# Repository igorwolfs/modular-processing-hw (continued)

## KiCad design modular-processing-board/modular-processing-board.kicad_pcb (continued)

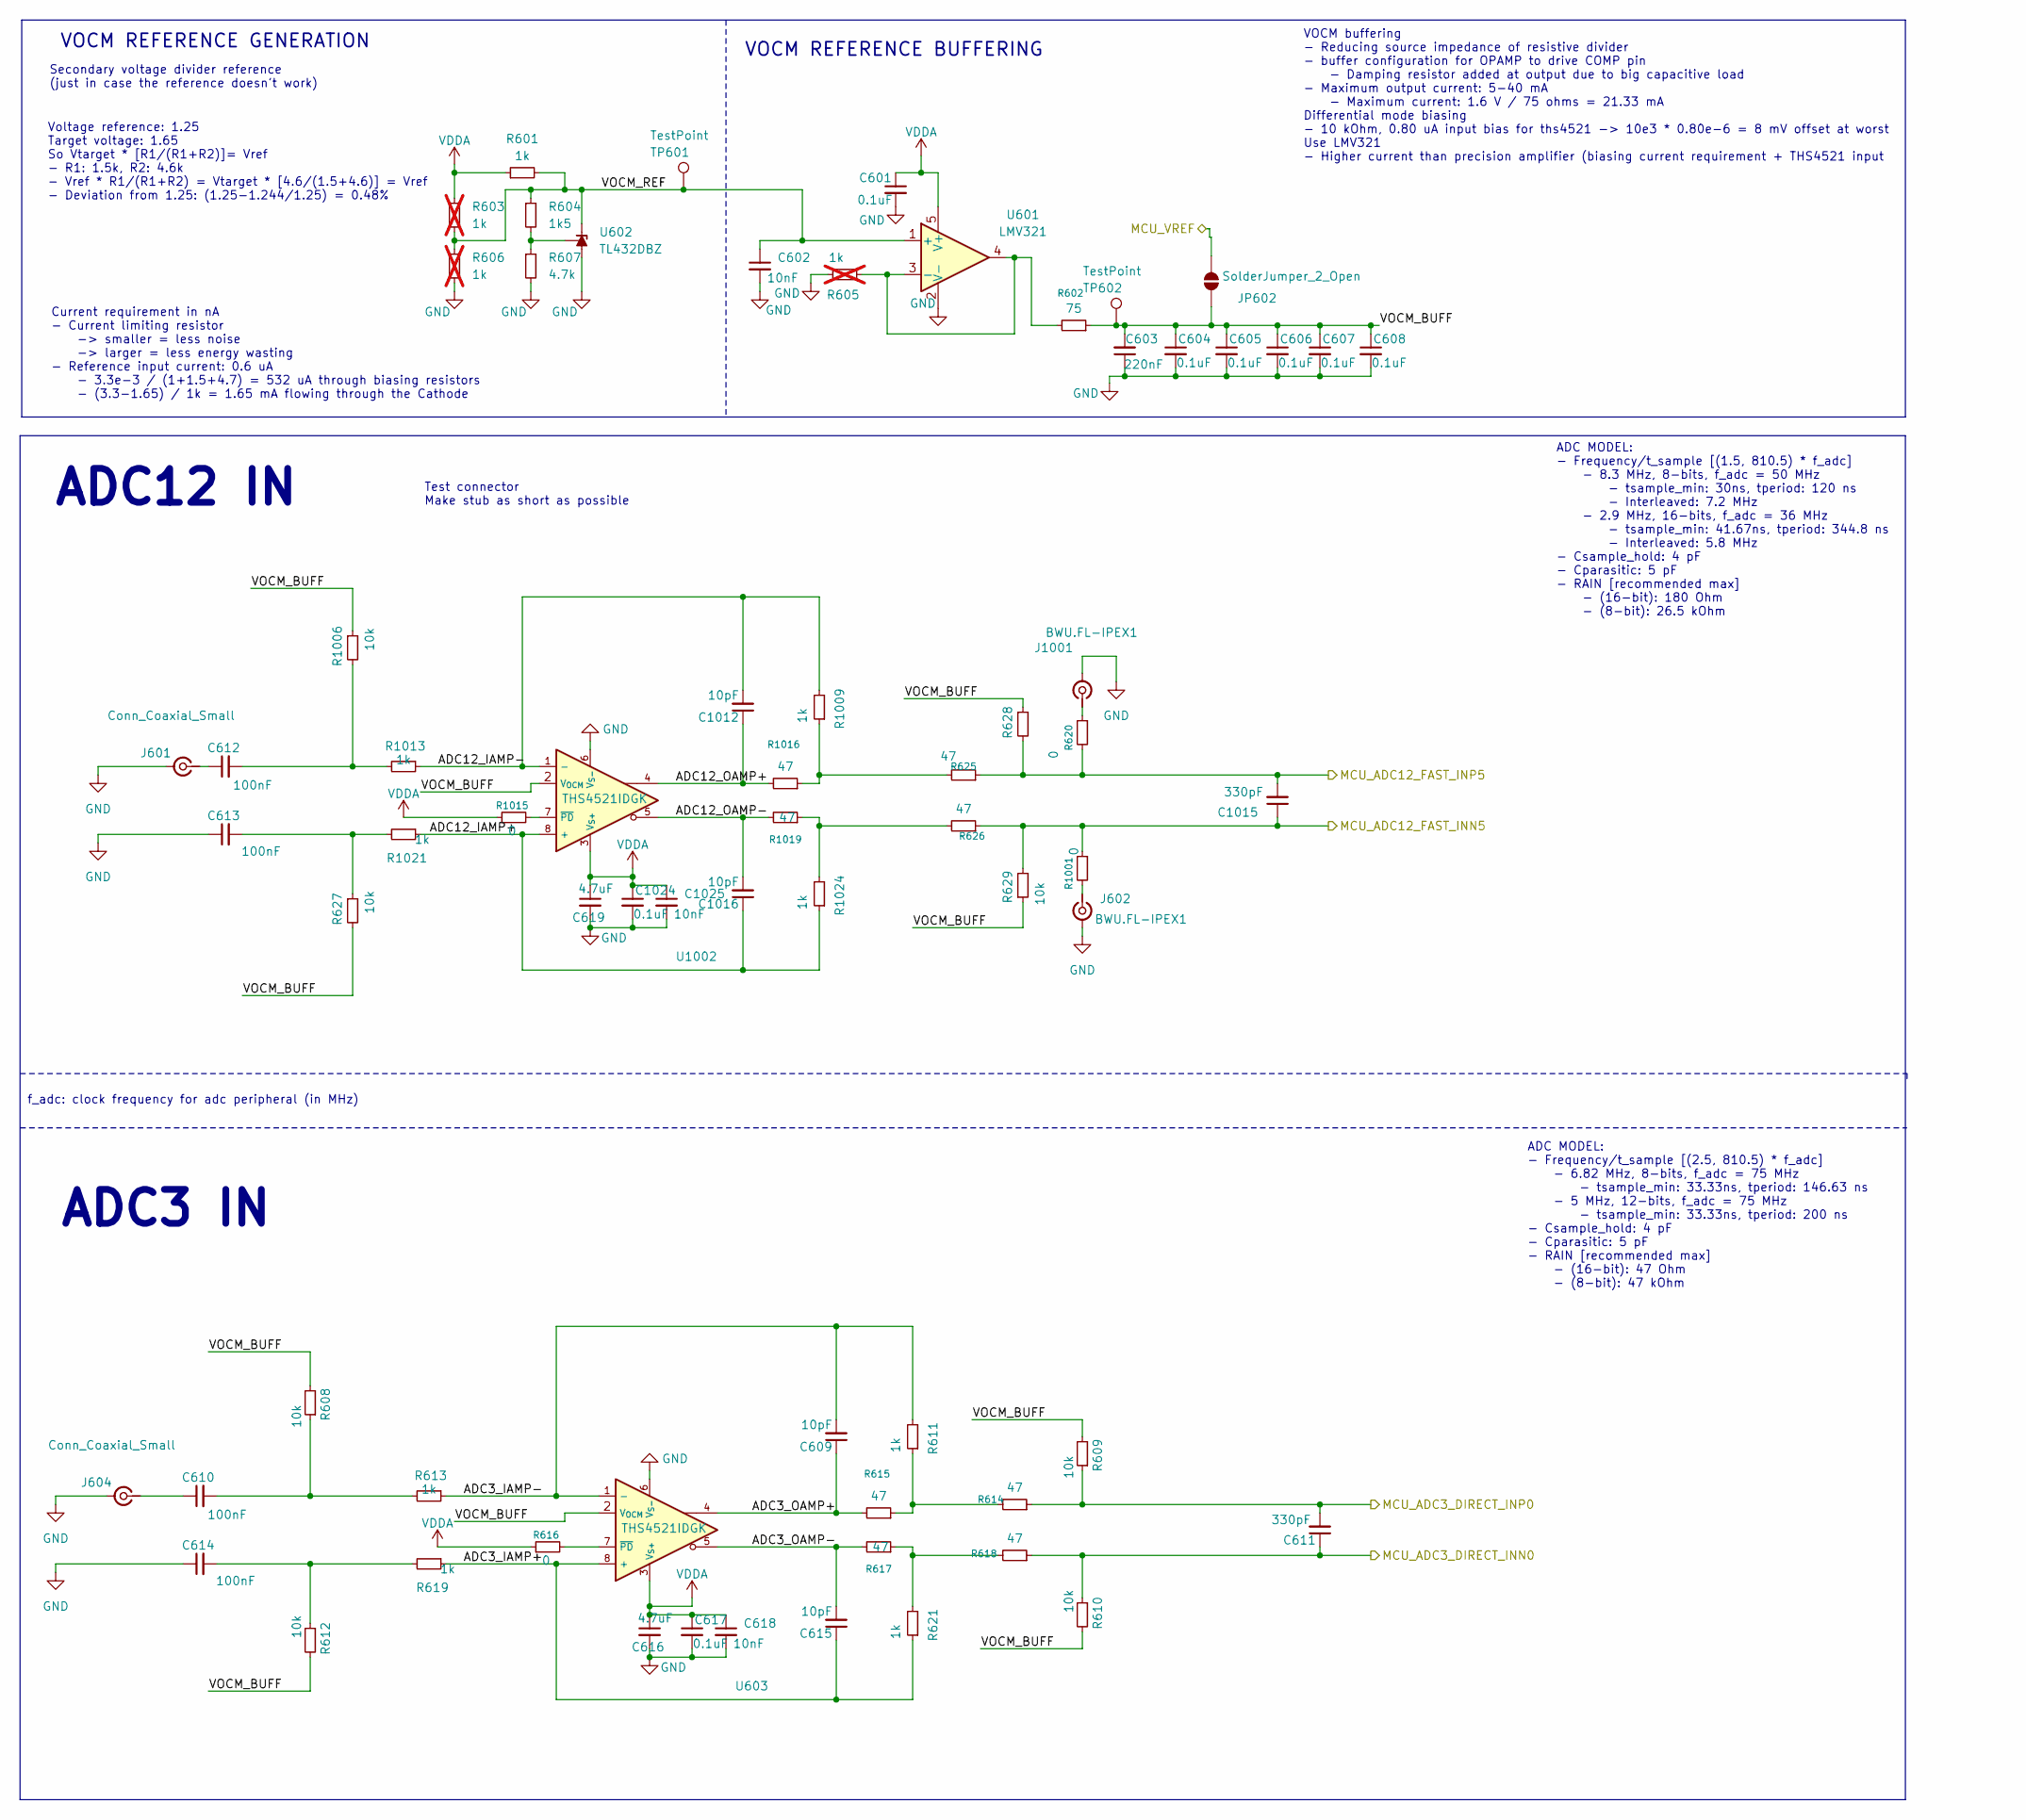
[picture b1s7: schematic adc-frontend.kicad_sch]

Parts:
C601, C604, C605, C606, C607, C608, C617, C1024: 0.1uF; C_0402_1005Metric; MPN CL05B104KB54PNC
C602, C618, C1025: 10nF; C_0402_1005Metric; MPN CL05B103KB5NNNC
C603: 220nF; C_0402_1005Metric; MPN CL05B224KO5NNNC
C609, C615, C1012, C1016: 10pF; C_0603_1608Metric_Pad1.08x0.95mm_HandSolder; MPN CL10C100JB8NNNC
C610, C612, C613, C614: 100nF; C_0603_1608Metric; MPN CC0603KRX7R9BB104
C611, C1015: 330pF; C_0603_1608Metric_Pad1.08x0.95mm_HandSolder; MPN CL10C331JB8NNNC
C616, C619: 4.7uF; C_0402_1005Metric; MPN CL05A475MP5NRNC
J601, J604: Conn_Coaxial_Small; SMA_Amphenol_901-144_Vertical; MPN BWSMA-KE-Z001
J602, J1001: BWU.FL-IPEX1; MPN BWU.FL-IPEX1
JP602: SolderJumper_2_Open; SolderJumper-2_P1.3mm_Open_Pad1.0x1.5mm
R601, R611, R613, R619, R621, R1009, R1013, R1021, R1024: 1k; R_0603_1608Metric; MPN 0603WAF1001T5E
R602: 75; R_0603_1608Metric; MPN 0603WAF750JT5E
R603, R605, R606: 1k; R_0603_1608Metric; MPN 0603WAF1001T5E; not fitted
R604: 1k5; R_0603_1608Metric; MPN 0603WAF1501T5E
R607: 4.7k; R_0603_1608Metric; MPN 0603WAF4701T5E
R608, R609, R610, R612, R627, R628, R629, R1006: 10k; R_0603_1608Metric; MPN 0603WAF1002T5E
R614, R615, R617, R618, R625, R626, R1016, R1019: 47; R_0603_1608Metric; MPN 0603WAF470JT5E
R616, R620, R1001, R1015: 0; R_0603_1608Metric; MPN 0603WAF0000T5E
TP601, TP602: TestPoint; PinSocket_1x01_P1.27mm_Vertical
U601: LMV321; SOT-23-5; MPN LMV321IDBVR
U602: TL432DBZ; SOT-23; MPN TL432
U603, U1002: THS4521IDGK; VSSOP-8_3x3mm_P0.65mm; MPN THS4521IDGKR

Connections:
/adc-frontend/ADC3_IAMP+: C615.1, R619.1, R621.1, U603.8 (+)
/adc-frontend/ADC3_IAMP-: C609.2, R611.2, R613.1, U603.1 (-)
/adc-frontend/ADC3_OAMP+: C609.1, R615.2, U603.4
/adc-frontend/ADC3_OAMP-: C615.2, R617.2, U603.5
/adc-frontend/ADC12_IAMP+: C1016.1, R1021.1, R1024.1, U1002.8 (+)
/adc-frontend/ADC12_IAMP-: C1012.2, R1009.2, R1013.1, U1002.1 (-)
/adc-frontend/ADC12_OAMP+: C1012.1, R1016.2, U1002.4
/adc-frontend/ADC12_OAMP-: C1016.2, R1019.2, U1002.5
/adc-frontend/MCU_ADC3_DIRECT_INN0: C611.1, R610.1, R618.1; also elsewhere on the board
/adc-frontend/MCU_ADC3_DIRECT_INP0: C611.2, R609.1, R614.1; also elsewhere on the board
/adc-frontend/MCU_ADC12_FAST_INN5: C1015.1, R626.1, R629.2, R1001.1; also elsewhere on the board
/adc-frontend/MCU_ADC12_FAST_INP5: C1015.2, R620.2, R625.1, R628.2; also elsewhere on the board
/adc-frontend/MCU_VREF: JP602.2 (B); also elsewhere on the board
/adc-frontend/VOCM_BUFF: C603.2, C604.1, C605.1, C606.1, C607.1, C608.1, JP602.1 (A), R602.1, R608.2, R609.2, R610.2, R612.2, R627.2, R628.1, R629.1, R1006.1, TP602.1, U603.2 (V_{OCM}), U1002.2 (V_{OCM})
/adc-frontend/VOCM_REF: C602.1, R601.2, R603.2, R604.1, R606.1, TP601.1, U601.1 (+), U602.2 (K)
GND: C601.2, C602.2, C603.1, C604.2, C605.2, C606.2, C607.2, C608.2, C613.1, C614.1, C616.2, C617.2, C618.2, C619.2, C1024.2, C1025.2, J601.2 (Ext), J602.2 (Ext), J604.2 (Ext), J1001.2 (Ext), R605.1, R606.2, R607.2, U601.2 (V-), U602.3 (A), U603.6 (V_{S-}), U1002.6 (V_{S-}); also elsewhere on the board
unnamed: C610.2, R608.1, R613.2
unnamed: C612.2, R1006.2, R1013.2
unnamed: C613.2, R627.1, R1021.2
unnamed: C614.2, R612.1, R619.2
unnamed: C612.1, J601.1 (In)
unnamed: J602.1 (In), R1001.2
unnamed: C610.1, J604.1 (In)
unnamed: J1001.1 (In), R620.1
unnamed: R611.1, R614.2, R615.1
unnamed: R617.1, R618.2, R621.2
unnamed: R625.2, R1009.1, R1016.1
unnamed: R626.2, R1019.1, R1024.2
unnamed: R602.2, R605.2, U601.3 (-), U601.4
unnamed: R604.2, R607.1, U602.1 (REF)
unnamed: R616.2, U603.7 (~PD)
unnamed: R1015.2, U1002.7 (~PD)
VDDA: C601.1, C616.1, C617.1, C618.1, C619.1, C1024.1, C1025.1, R601.1, R603.1, R616.1, R1015.1, U601.5 (V+), U603.3 (V_{S+}), U1002.3 (V_{S+}); also elsewhere on the board

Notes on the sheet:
ADC MODEL: - Frequency/t_sample [(1.5, 810.5) * f_adc] - 8.3 MHz, 8-bits, f_adc = 50 MHz - tsample_min: 30ns, tperiod: 120 ns - Interleaved: 7.2 MHz - 2.9 MHz, 16-bits, f_adc = 36 MHz - tsample_min: 41.67ns, tperiod: 344.8 ns - Interleaved: 5.8 MHz - Csample_hold: 4 pF - Cparasitic: 5 pF - RAIN [re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
VOCM REFERENCE GENERATION
ADC12 IN
Voltage reference: 1.25 Target voltage: 1.65 So Vtarget * [R1/(R1+R2)]= Vref - R1: 1.5k, R2: 4.6k - Vref * R1/(R1+R2) = Vtarget * [4.6/(1.5+4.6)] = Vref - Deviation from 1.25: (1.25-1.244/1.25) = 0.48%
VOCM REFERENCE BUFFERING
Secondary voltage divider reference (just in case the reference doesn't work)
Test connector Make stub as short as possible
ADC MODEL: - Frequency/t_sample [(2.5, 810.5) * f_adc] - 6.82 MHz, 8-bits, f_adc = 75 MHz - tsample_min: 33.33ns, tperiod: 146.63 ns - 5 MHz, 12-bits, f_adc = 75 MHz - tsample_min: 33.33ns, tperiod: 200 ns - Csample_hold: 4 pF - Cparasitic: 5 pF - RAIN [recommended max] - (16-bit): 47 Ohm - (8-bit)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
VOCM buffering - Reducing source impedance of resistive divider - buffer configuration for OPAMP to drive COMP pin - Damping resistor added at output due to big capacitive load - Maximum output current: 5-40 mA - Maximum current: 1.6 V / 75 ohms = 21.33 mA Differential mode biasing - 10 kOhm, 0.80 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
Current requirement in nA - Current limiting resistor -> smaller = less noise -> larger = less energy wasting - Reference input current: 0.6 uA - 3.3e-3 / (1+1.5+4.7) = 532 uA through biasing resistors - (3.3-1.65) / 1k = 1.65 mA flowing through the Cathode
f_adc: clock frequency for adc peripheral (in MHz)
ADC3 IN

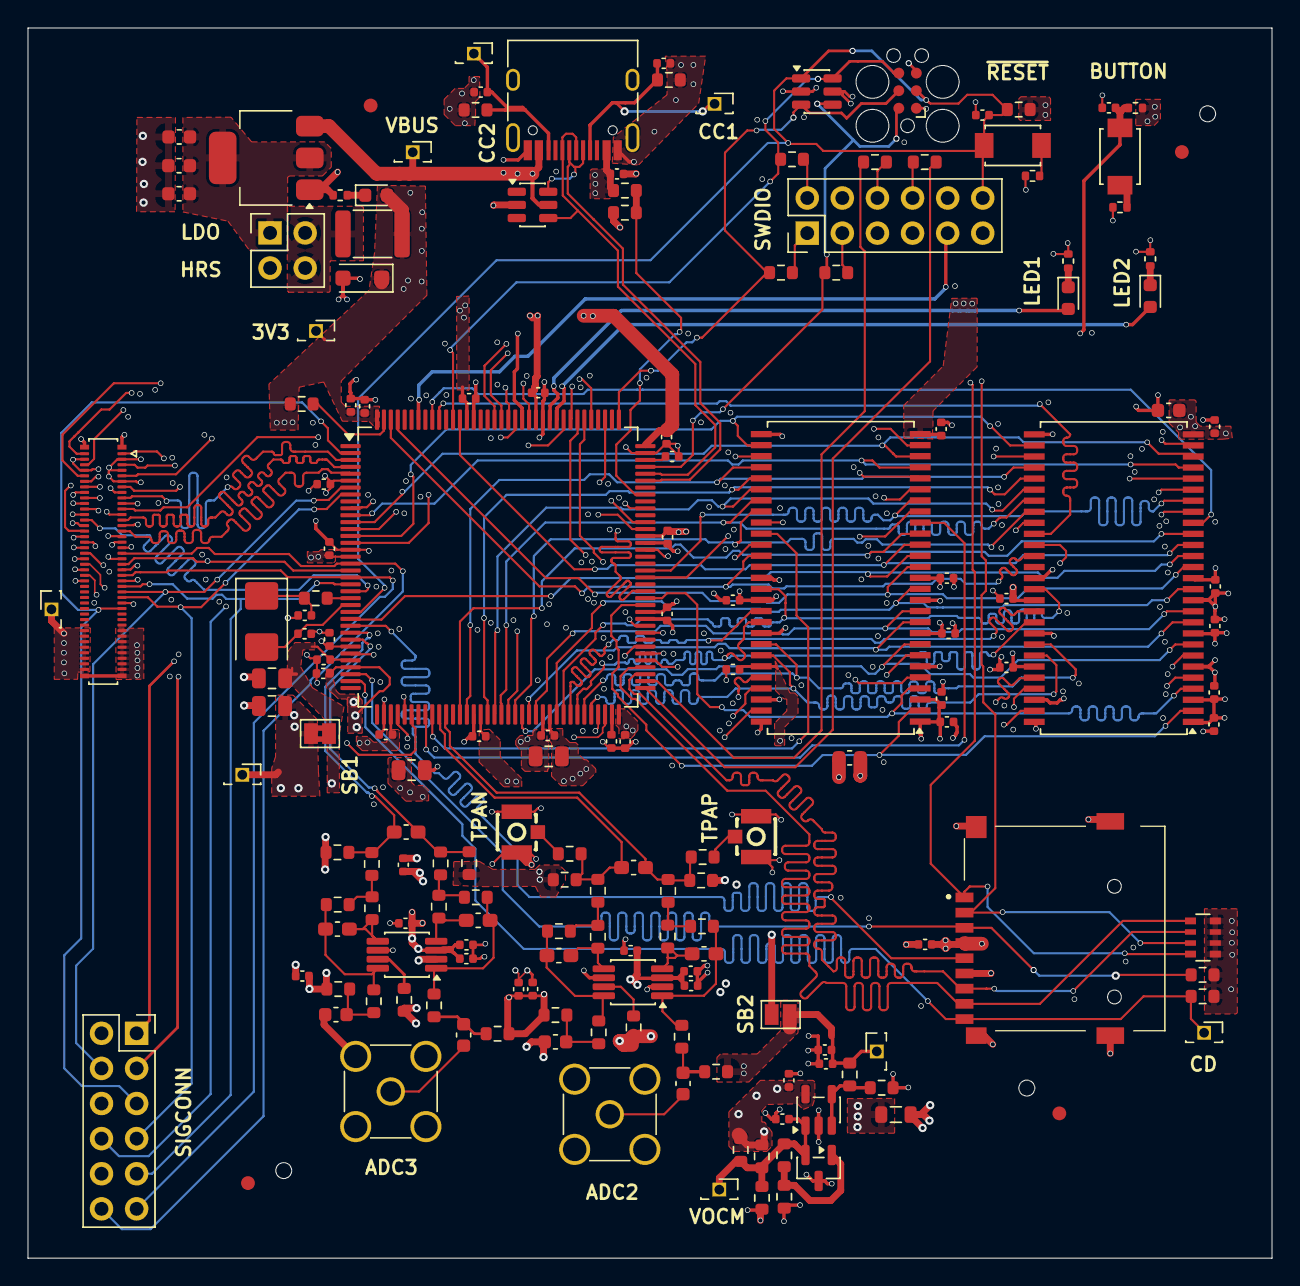
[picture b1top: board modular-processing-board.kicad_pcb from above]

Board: 6 copper layers, 90.0 x 89.0 mm, 177 parts (0 on the bottom side), 145 nets.

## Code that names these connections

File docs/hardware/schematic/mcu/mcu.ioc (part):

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Mcu.Name=STM32H723ZGTx
Mcu.Package=LQFP144
Mcu.UserName=STM32H723ZGTx
PA0.Mode=SD_4_bits_Wide_bus
PA0.Signal=SDMMC2_CMD
PA1.GPIOParameters=GPIO_Label
PA1.GPIO_Label=IO_SDMMC_CD
PA1.Signal=GPIO_Input
PA11.Mode=Device_Only_FS
PA11.Signal=USB_OTG_HS_DM
PA12.Mode=Device_Only_FS
PA12.Signal=USB_OTG_HS_DP
PA13(JTMS/SWDIO).Mode=Trace_Asynchronous_SW
PA13(JTMS/SWDIO).Signal=DEBUG_JTMS-SWDIO
PA14(JTCK/SWCLK).Mode=Trace_Asynchronous_SW
PA14(JTCK/SWCLK).Signal=DEBUG_JTCK-SWCLK
PA4.Mode=PSSI_16
PA4.Signal=PSSI_DE
PA5.Mode=PSSI_16
PA5.Signal=PSSI_D14
PA6.Mode=PSSI_16
PA6.Signal=PSSI_PDCK
PA9.GPIOParameters=GPIO_Label
PA9.GPIO_Label=USB_SENSE
PA9.Signal=GPIO_Input
PB0.Signal=ADCx_INN5
PB1.Signal=ADCx_INP5
PB10.Mode=I2C
PB10.Signal=I2C2_SCL
PB11.Mode=I2C
PB11.Signal=I2C2_SDA
PB12.Mode=Asynchronous
PB12.Signal=UART5_RX
PB13.Mode=Asynchronous
PB13.Signal=UART5_TX
PB14.Mode=SD_4_bits_Wide_bus
PB14.Signal=SDMMC2_D0
PB15.Mode=SD_4_bits_Wide_bus
PB15.Signal=SDMMC2_D1
PB3(JTDO/TRACESWO).Mode=Trace_Asynchronous_SW
PB3(JTDO/TRACESWO).Signal=DEBUG_JTDO-SWO
PB5.Mode=SdramChipSelect2_2
PB5.Signal=FMC_SDCKE1
PB6.Mode=SdramChipSelect2_2
PB6.Signal=FMC_SDNE1
PC0.Signal=FMC_SDNWE
PC1.Mode=SD_4_bits_Wide_bus
PC1.Signal=SDMMC2_CK
PC10.Mode=PSSI_16
PC10.Signal=PSSI_D8
PC12.Mode=PSSI_16
PC12.Signal=PSSI_D9
PC13.GPIOParameters=GPIO_Label
PC13.GPIO_Label=PBOOST_EN
PC13.Signal=GPIO_Output
PC14-OSC32_IN.GPIOParameters=GPIO_Label
PC14-OSC32_IN.GPIO_Label=PSEPIC_EN
PC14-OSC32_IN.Signal=GPIO_Output
PC2_C.Mode=IN1-Differential
PC2_C.Signal=ADC3_INN1
PC3_C.Mode=IN1-Differential
PC3_C.Signal=ADC3_INP1
PC4.Mode=SdramChipSelect1_1
PC4.Signal=FMC_SDNE0
PC5.Mode=SdramChipSelect1_1
PC5.Signal=FMC_SDCKE0
PC6.Mode=PSSI_16
PC6.Signal=PSSI_D0
PC7.Mode=PSSI_16
PC7.Signal=PSSI_D1
PC9.Mode=PSSI_16
PC9.Signal=PSSI_D3
PD0.Signal=FMC_D2_DA2
PD1.Signal=FMC_D3_DA3
PD10.Signal=FMC_D15_DA15
PD12.Mode=PSSI_16
PD12.Signal=PSSI_D12
PD13.Mode=PSSI_16
PD13.Signal=PSSI_D13
PD14.Signal=FMC_D0_DA0
PD15.Signal=FMC_D1_DA1
PD2.Mode=PSSI_16
PD2.Signal=PSSI_D11
PD3.Mode=PSSI_16
PD3.Signal=PSSI_D5
PD4.GPIOParameters=GPIO_Label
PD4.GPIO_Label=LED2
PD4.Signal=GPIO_Output
PD5.GPIOParameters=GPIO_Label
PD5.GPIO_Label=LED1
PD5.Signal=GPIO_Output
PD6.Mode=PSSI_16
PD6.Signal=PSSI_D10
PD7.GPIOParameters=GPIO_Label
PD7.GPIO_Label=BUTTON_1
PD7.Signal=GPIO_Input
PD8.Signal=FMC_D13_DA13
PD9.Signal=FMC_D14_DA14
PE0.Signal=FMC_NBL0
PE1.Signal=FMC_NBL1
PE10.Signal=FMC_D7_DA7
PE11.Signal=FMC_D8_DA8
PE12.Signal=FMC_D9_DA9
PE13.Signal=FMC_D10_DA10
PE14.Signal=FMC_D11_DA11
PE15.Signal=FMC_D12_DA12
PE3.GPIOParameters=GPIO_Label
PE3.GPIO_Label=ADC_ALERT
PE3.Signal=GPIO_Input
PE4.Mode=PSSI_16
PE4.Signal=PSSI_D4
PE5.Mode=PSSI_16
PE5.Signal=PSSI_D6
PE6.Mode=PSSI_16
PE6.Signal=PSSI_D7
PE7.Signal=FMC_D4_DA4
PE8.Signal=FMC_D5_DA5
PE9.Signal=FMC_D6_DA6
PF0.Signal=FMC_A0
PF1.Signal=FMC_A1
PF10.Mode=PSSI_16
PF10.Signal=PSSI_D15
PF11.Signal=FMC_SDNRAS
PF12.Signal=FMC_A6
PF13.Signal=FMC_A7
PF14.Signal=FMC_A8
PF15.Signal=FMC_A9
PF2.Signal=FMC_A2
PF3.Signal=FMC_A3
PF4.Signal=FMC_A4
PF5.Signal=FMC_A5
PF6.Mode=PWM Generation1 CH1
PF6.Signal=TIM23_CH1
PF7.Signal=S_TIM23_CH2
PF8.Signal=S_TIM23_CH3
PF9.Signal=S_TIM23_CH4
PG0.Signal=FMC_A10
PG1.Signal=FMC_A11
PG10.Mode=PSSI_16
PG10.Signal=PSSI_D2
PG11.Mode=SD_4_bits_Wide_bus
PG11.Signal=SDMMC2_D2
PG12.Mode=SD_4_bits_Wide_bus
PG12.Signal=SDMMC2_D3
PG15.Signal=FMC_SDNCAS
PG2.Signal=FMC_A12
PG4.Signal=FMC_A14_BA0
PG5.Signal=FMC_A15_BA1
PG8.Signal=FMC_SDCLK
PG9.Mode=PSSI_16
PG9.Signal=PSSI_RDY
PH0-OSC_IN.Mode=HSE-External-Oscillator
PH0-OSC_IN.Signal=RCC_OSC_IN
PH1-OSC_OUT.Mode=HSE-External-Oscillator
PH1-OSC_OUT.Signal=RCC_OSC_OUT
RCC.HSE_VALUE=25000000
RCC.SYSCLKFreq_VALUE=64000000
board=custom

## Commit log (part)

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2025-10-07 minor comments (next) pick RAM, add connectors
2025-10-07 added notes on ram variants (next) research RAM pinouts and possible RAM IC's usable
2025-10-11 research on best communication interfaces, added sdram
2025-10-12 basicsic pinout/component selection done, added SDRAM pins (next) Add parallel pins, add connections to pinheaders
2025-10-12 added parallel slave bus, SWO, USB (next) add small PSU for CPU-board, add ethernet PHY, add correct USB connector
2025-10-14 added ESD protection, USB connector, SD-CARD, decoupling caps (next) add appropriate VREF, COAX for ADC, board2board connectors and connect wiring
2025-10-14 added new, better suited possible connectors
2025-10-18 decided on fully differential configuratinon with ths4521 for both ADC inputs
2025-10-19 Finished basic HW (next) Fix-up all labeling, then start laying out
2025-10-23 completed schematic
2025-10-25 various changes to schematic (next) add bias resistors after testing results on acoustic-carrier-board
2025-10-28 started layout
2025-10-30 removed power input jumpers to single one, added trace impedances and production restrictions (next) route sdram
2025-11-04 figuring out delay matching for sdram
2025-11-06 checked timing for sdram, routing
2025-11-07 rough length mamatching for sdram (next) route PSSI-bus
2025-11-09 replaced sdmmc connector, added smmc trace, added u.fl. connectors
2025-11-09 redid frontend layout, routed diff adc wires (next) finish routing, start with decoupling and planes
2025-11-09 reconnected vref
2025-11-10 routing hardware (next) reroute the CLK and A12
2025-11-13 added GND conconnections (next) remove 8th layer
2025-11-15 layed out most components (next) cadd vias for impedance reduction for high-speed signals, check impedance of signals
2025-11-16 changeed layer 3 traces to 50 ohm-impedance tracks
2025-11-16 added return vias, solved routing errors (next) check impedance of top-bottom layer signals, schematic check
2025-11-16 completed schematic + layout (next) do footprint checks etc.
2025-11-18 checking SDMMC SD-card interface (next) finish checking sd-card holder, check connectors, frontend and power
2025-11-19 finished schematic checks, added extra capacitors on LDO output (next) add holes to board / board shape, do layout checks
2025-11-20 checked components part numbers (next) board checks
2025-11-20 matched PSSI bus lenghts
2025-11-22 finished sdram length matching (next) check trace closeness for ADC-signals, check impedances, check SDMMC lengths
2025-11-22 checked differential impedances + SDMMC lenghts (next) check impedances of SE-signals
2025-11-23 finish modular-processing-hw board checks, prepare gerbers for manufacturing and perform checks
2025-11-23 minor changes in BOM and DNP-components
2025-11-26 changed footprints (next) try uploading to jlcpcb for manufacturing, change crystal if required for economic assembly
2025-11-28 processing hw submitted
2025-11-28 sending in for manufacturing
2025-11-30 second version sent in
2025-12-02 [hw] Merged zones, redrew traces for minimal impedance modification (next) recheck all SDRAM traces + PSSI traces
2025-12-02 finalized layout for 3rd submission attempt to jlc
2025-12-03 changed testpoints
2025-12-03 changed header of pos-file
2025-12-18 added firmware
2026-05-17 minor change in fw
